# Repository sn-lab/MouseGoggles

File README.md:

**MouseGoggles**: A dual-SPI-display mouse-sized VR headset for mouse neuroscience and behavior research, powered by Raspberry Pi and the Godot game engine. Check out the paper at Nature Methods! https://www.nature.com/articles/s41592-024-02540-y

- Find a bug, have a suggestion, or want to make a feature request? Submit an [issue](https://github.com/sn-lab/MouseGoggles/issues) or start a [discussion](https://github.com/sn-lab/MouseGoggles/discussions)!

**Work in progess**

* Updating and improving [MouseGoggles EyeTrack 2.0](https://github.com/sn-lab/MouseGoggles/tree/main/Versions/EyeTrack/2.0) eye imaging quality and software improvements.

**Previous Updates**

* (Jan 2026) Added intial files for [MouseGoggles EyeTrack 2.0](https://github.com/sn-lab/MouseGoggles/tree/main/Versions/EyeTrack/2.0)! The design is now built around a single Raspberry Pi 5, aiming toward improving eye-tracking quality and a simpler assembly process (though eye-imaging quality is still being worked on).
  
* (May 2025) Big software updates to EyeTrack 1.1, including the first Godot project (2.1) which enables controlling and viewing the eye-tracking cameras from within the game engine! TCP/UDP communication between the Pis enable TTL outputs and eye-tracking videos to be controlled directly from VR experiment scripts.

* (Mar 2024) Added the [MouseGoggles EyeTrack](https://github.com/sn-lab/MouseGoggles/tree/main/Versions/EyeTrack/1.0) headset, for binocular eye/pupil tracking cameras integrated into the headset

# Building a MouseGoggles System

All versions of MouseGoggles were designed using as many readily available, off-the-shelf parts as possible, with only a minimal number of custom parts required to make assembly as simple as possible. To build a MouseGoggles system, navigate to the folder of the version you'd like to build in the [Versions](https://github.com/sn-lab/MouseGoggles/tree/main/Versions) folder and follow the included README for a comprehensive parts list, assembly guide, and software installation instructions. Since some parts included in earlier versions of the system have since been discontinued by the manufacturers, [Eyetrack version 2.0](https://github.com/sn-lab/MouseGoggles/tree/main/Versions/EyeTrack/2.0) is what we recommend building for all use-cases. Version 2.0 is built on an entirely new display platform (Raspberry Pi 5; mipi-dbi-spi) that future versions will be developed from. 

# About MouseGoggles

### The Raspberry Pi and Godot game engine

The heart of the MouseGoggles system is a [Raspberry Pi 4](https://www.raspberrypi.com/products/raspberry-pi-4-model-b/) running the [Godot](https://godotengine.org/) video game engine. Since the displays are relatively low resolution (240x240), an inexpensive single-board computer like a Raspberry Pi 4 is all that's needed to effectively render visual scenes at high (>=60 fps) framerates. The multiplatform game engine Godot makes it easy to create virtual scenes and develop experimental protocols. Examples included in this repo are experiments for visual cliff avoidance, reactions to looming stimuli of various size/velocity ratios, and the syndirectional rotational optomotor response to gratings of various spatial wavelengths. The views rendered for each display are controlled by separate in-game cameras which can be tied together to match the inter-eye distance and angle of a typical mouse. Custom display shaders warp the view from each camera to match the spherical distortion of the Fresnel lenses, intended to create a realistic and immersive experience for the mouse.

### The display driver

Based on a ["blazing fast" display driver](https://github.com/juj/fbcp-ili9341) for SPI-based displays, the driver included in this repository works by copying the HDMI framebuffer and streaming the image data to the connected displays connected on the Raspberry Pi's SPI port. This means that the headset displays are not limited to displaying what is rendered by Godot; in fact, whatever is displayed on the central 240x420 (WxH) pixel region of the screen is going to be streamed to the displays. If you want to create images or video with some other program, you just have to position it in the center of the display for it to be sent to the displays -- the top 240x210 sent to display 0 (on SPI0 chip-select 0) and the bottom 240x210 to display 1 (on SPI0 chip-select 1).

### The MouseGoggles 1.0 headset

To create an immersive, wide field-of-view (FOV) VR headset from the dual-display Raspberry Pi, a 3D-printed headset case angles the displays inwards and sets them behind Fresnel lenses. These lenses serve two functions: to allow the displays to be positioned very close (<15 mm) to the mouse's eyes while still maintaining a comfortable infinity focal distance, and to spherically distort the displays to cover a wide FOV around each eye. Viewing angles from 0-70 degrees (0-52.5 degrees on the chipped side of the circular display) are linearly mapped onto the 240x210 circular display, resulting in an angular resolution of ~0.64 deg/pixel. With the 2 displays angled 45 degrees inward from straight ahead, the binocular headset covers a wide FOV: 140 degrees vertical and 230 degrees horizontal, with ~25 degrees of binocular overlap. Even greater horizontal FOVs are possible with greater display angles. This headset is the first official version of MouseGoggles (1.0), but newer versions have been developed which add new functionality, such as a smaller form-factor headset detached from the Raspberry Pi (1.1-1.2, 1.5), adjustable inter-eye distance (1.2-1.5), and an easier to assemble design (1.5). For more details on each MouseGoggles version, see the [Versions](https://github.com/sn-lab/MouseGoggles/tree/main/Versions) folder.

### MouseGoggles Mono 1.0

In addition to the binocular MouseGoggles system, a monocular eyepiece version can be built using a single display, lens, and microcontroller. Where the headset is ideal for complex virtual reality experiments and behavioral research, the monocular display is ideal for simple visual stimulation for basic visual neuroscience applications. The fast microcontroller [Teensy4.0](https://www.pjrc.com/store/teensy40.html) and [Adafruit graphics library](https://learn.adafruit.com/adafruit-gfx-graphics-library/overview) is used to display simple shapes and moving patterns such as drifting gratings and flickers. For more details, see [Versions/Mono/1.0]().

### Treadmills

The MouseGoggles VR headset was developed and tested using a two different treadmills for simulated walking: the spherical treadmill setup as described [here](https://pubmed.ncbi.nlm.nih.gov/19829374/) and the linear treadmill described [here](https://github.com/janelia-experimental-technology/Rodent-Belt-Treadmill/tree/main). These treadmills use sensors to detect treadmill motion and a microcontroller to transmit this movement information to external devices. By modifying the microcontroller code, we can adapt these systems to send treadmill motion to the Raspberry Pi over USB through computer mouse emulation. Forward movement (i.e. "pitch" of the spherical treadmill, or any movement of the linear treadmill) is mapped as mouse y movement, turning (i.e. "yaw" of the spherical treadmill) is mapped as x movement, and sideways motion (i.e. "roll" of the spherical treadmill) is mapped as mouse scroll wheel movement. The Godot game engine converts these detected mouse movement events into the corresponding camera movements in the virtual scene. This setup allows the human user to test the game environments and experiments using a standard computer mouse or touchpad, and to use this VR system with any type of treadmill control system that can be translated through the standard USB mouse communication protocol. To set up one of these treadmill systems with MouseGoggles (including adding a headbar and mount to head-fix a mouse above the treadmill), see the [README](https://github.com/sn-lab/MouseGoggles/blob/main/Other%20Hardware/Installation%20README.md) in the [Other Hardware](https://github.com/sn-lab/MouseGoggles/tree/main/Other%20Hardware) folder.

# Published Data

Multiple datasets have been collected for validating and testing different aspects of the MouseGoggles system for neuroscience applications, including 2-photon imaging for visual stimulation, hippocampal electrophysiology for place cell activity during virtual navigation, and video recordings of mouse behaviors during looming stimulus presentation. Check out our [preprint on Research Square](https://doi.org/10.21203/rs.3.rs-3301474/v1) for explanation and visualization of these datasets. Data, metadata, and code to process and analyze these datasets are included in the [Published Data](https://github.com/sn-lab/MouseGoggles/tree/main/Published%20Data) folder of this repository; large raw data files unsuitable for github are hosted on [Figshare](https://figshare.com/articles/dataset/Raw_image_files/24039021). 
To reproduce the published results from each of these datasets, follow the instructions in the [Description of Contents](https://github.com/sn-lab/MouseGoggles/blob/main/Published%20Data/Description%20of%20Contents.md) file, noting the software dependencies listed here:

```
* Matlab 2022b
* Python 2.8.8
* suite2p (suite2p.org)
* https://github.com/misaacson01/NoRMCorre
* https://github.com/lolaBerkowitz/SNLab_ephys
* https://github.com/nelpy/nelpy
* https://github.com/ryanharvey1/neuro_py
* https://github.com/ryanharvey1/ripple_heterogeneity
```

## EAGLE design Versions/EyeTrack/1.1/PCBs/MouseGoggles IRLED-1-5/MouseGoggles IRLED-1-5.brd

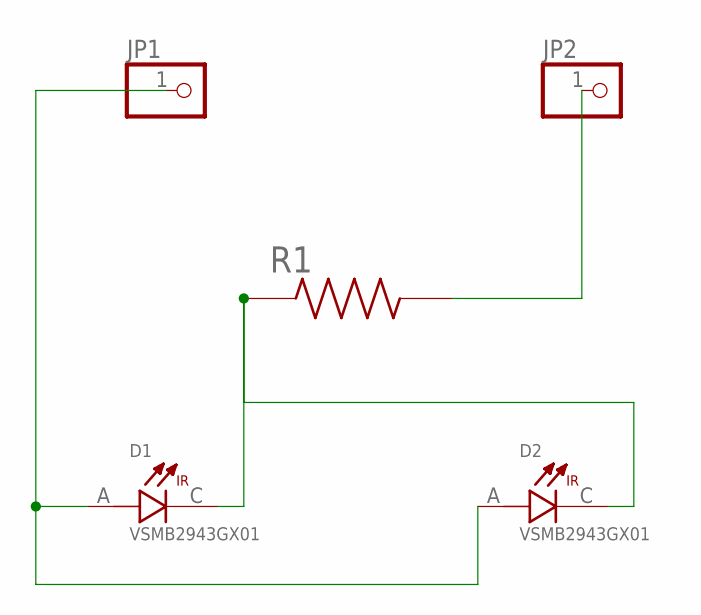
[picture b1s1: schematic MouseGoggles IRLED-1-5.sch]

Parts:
D1, D2: VSMB2943GX01; DIO_VSMB2943GX01
JP1, JP2: PINHD-1X1; 1X01
R1: RC0805FR-07100RL; RESC2012X60N

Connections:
unnamed: JP2.1, R1.2
unnamed: D1.A, D2.A, JP1.1
unnamed: D1.C, D2.C, R1.1

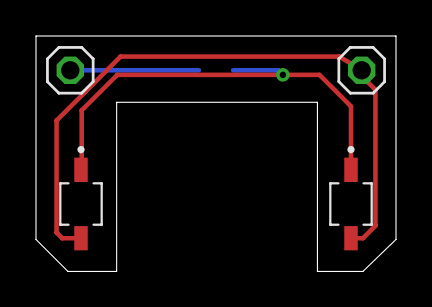
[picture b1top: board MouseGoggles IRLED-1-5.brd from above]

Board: 2 copper layers, 20.0 x 13.1 mm, 5 parts (1 on the bottom side), 3 nets.

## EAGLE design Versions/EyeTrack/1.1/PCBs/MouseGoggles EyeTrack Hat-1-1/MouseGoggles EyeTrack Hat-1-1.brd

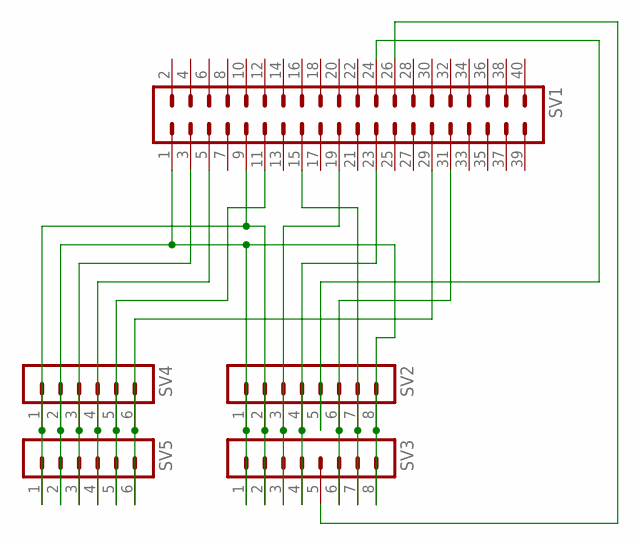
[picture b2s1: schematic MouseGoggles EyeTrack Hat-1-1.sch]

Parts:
SV1: MA20-2
SV2, SV3: MA08-1
SV4, SV5: MA06-1

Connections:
unnamed: SV1.1, SV2.1, SV2.8, SV3.1, SV3.8, SV4.2, SV5.2
unnamed: SV1.9, SV2.2, SV3.2, SV4.1, SV5.1
unnamed: SV1.19, SV2.3, SV3.3
unnamed: SV1.23, SV2.4, SV3.4
unnamed: SV1.24, SV2.5
unnamed: SV1.26, SV3.5
unnamed: SV1.31, SV2.6, SV3.6
unnamed: SV1.15, SV2.7, SV3.7
unnamed: SV1.3, SV4.3, SV5.3
unnamed: SV1.5, SV4.4, SV5.4
unnamed: SV1.11, SV4.5, SV5.5
unnamed: SV1.29, SV4.6, SV5.6

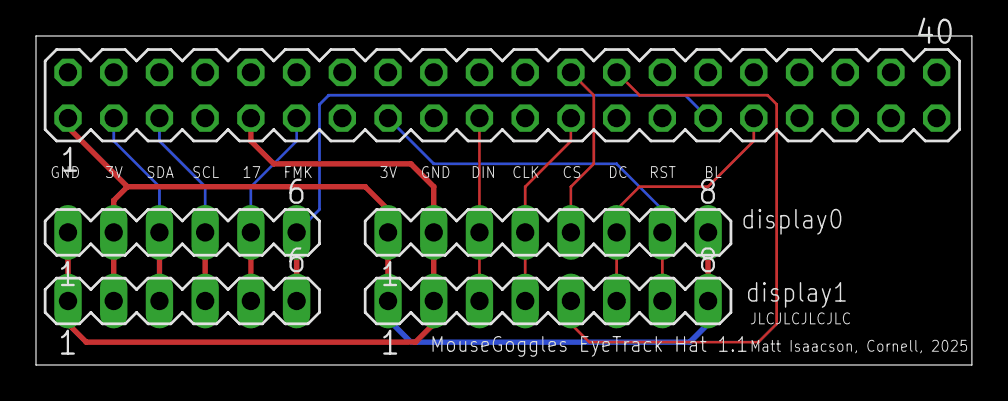
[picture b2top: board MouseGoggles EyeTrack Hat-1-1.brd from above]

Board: 2 copper layers, 52.0 x 18.3 mm, 5 parts (0 on the bottom side), 12 nets.

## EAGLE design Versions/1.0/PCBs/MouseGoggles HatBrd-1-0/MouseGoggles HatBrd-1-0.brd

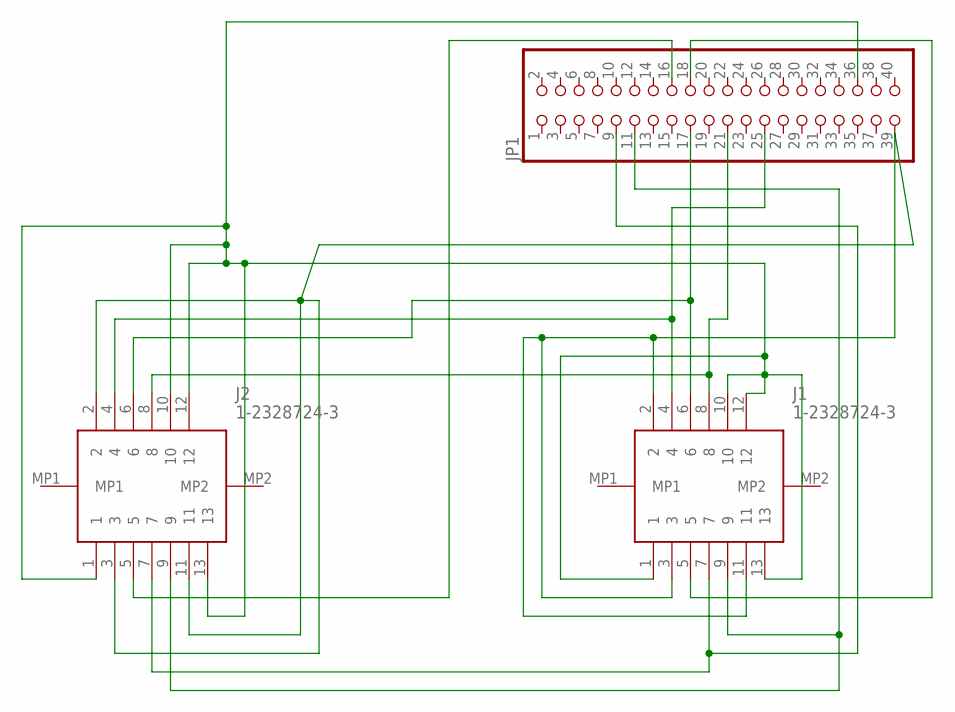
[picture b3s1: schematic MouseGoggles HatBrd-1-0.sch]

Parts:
J1, J2: 1-2328724-3; 123287243
JP1: PINHD-2X20-BIG; 2X20-BIG

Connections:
unnamed: J1.2, J1.3, J1.11, J2.2, J2.3, J2.11, JP1.39
unnamed: J1.8, J2.8, JP1.21
unnamed: J1.6, J2.6, JP1.17
unnamed: J1.5, JP1.18
unnamed: J1.1, J1.10, J1.12, J1.13, J2.1, J2.10, J2.12, J2.13, JP1.36
unnamed: J1.4, J2.4, JP1.25
unnamed: J1.7, J2.7, JP1.9
unnamed: J1.9, J2.9, JP1.11
unnamed: J2.5, JP1.16

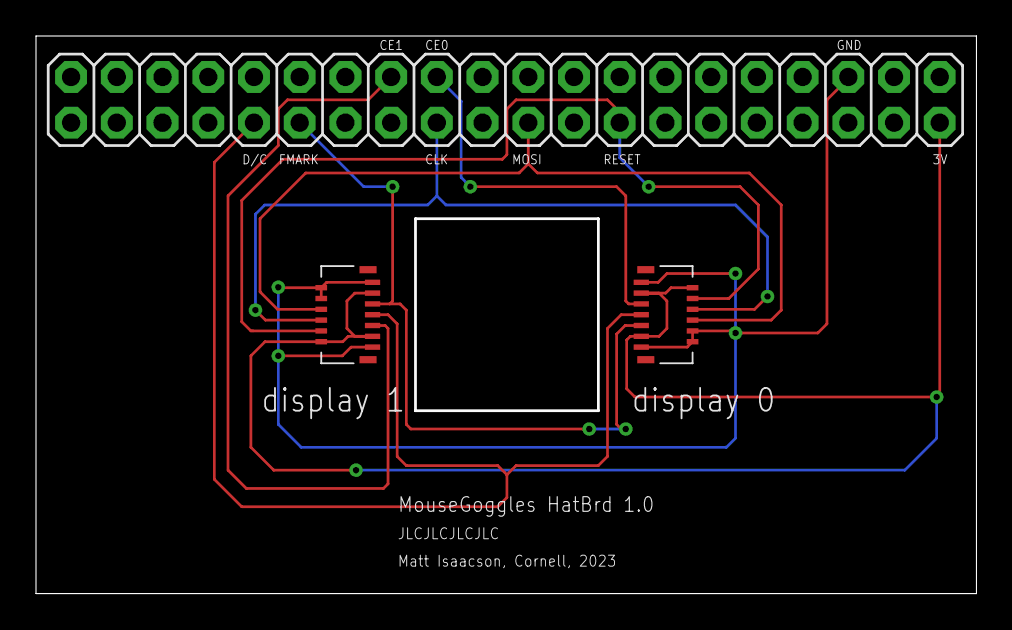
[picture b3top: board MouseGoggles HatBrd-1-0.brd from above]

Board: 2 copper layers, 52.1 x 30.8 mm, 3 parts (0 on the bottom side), 9 nets.

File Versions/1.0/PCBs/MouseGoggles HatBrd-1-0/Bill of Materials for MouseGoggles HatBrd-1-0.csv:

Comment,Designator,Package,JLCPCB Part #
FPC-CONN,J1,-,C3170061
FPC-CONN,J2,-,C3170061

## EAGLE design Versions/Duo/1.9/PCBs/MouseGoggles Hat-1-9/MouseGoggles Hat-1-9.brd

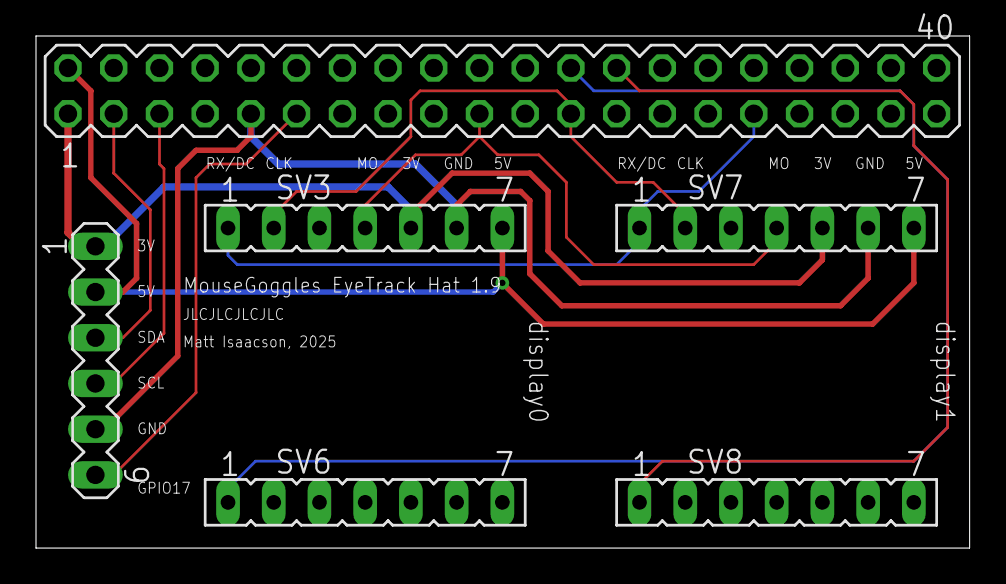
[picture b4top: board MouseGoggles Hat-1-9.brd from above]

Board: 2 copper layers, 51.9 x 28.4 mm, 6 parts (0 on the bottom side), 11 nets.

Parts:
SV1: MA20-2
SV3, SV6, SV7, SV8: FE07
SV4: MA06-1

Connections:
unnamed: SV1.1, SV3.5, SV4.1, SV7.5
unnamed: SV1.9, SV3.6, SV4.5, SV7.6
unnamed: SV1.23, SV3.2, SV7.2
unnamed: SV1.24, SV6.1
unnamed: SV1.26, SV8.1
unnamed: SV1.31, SV3.1, SV7.1
unnamed: SV1.19, SV3.4, SV7.4
unnamed: SV1.3, SV4.3
unnamed: SV1.5, SV4.4
unnamed: SV1.11, SV4.6
unnamed: SV1.2, SV3.7, SV4.2, SV7.7

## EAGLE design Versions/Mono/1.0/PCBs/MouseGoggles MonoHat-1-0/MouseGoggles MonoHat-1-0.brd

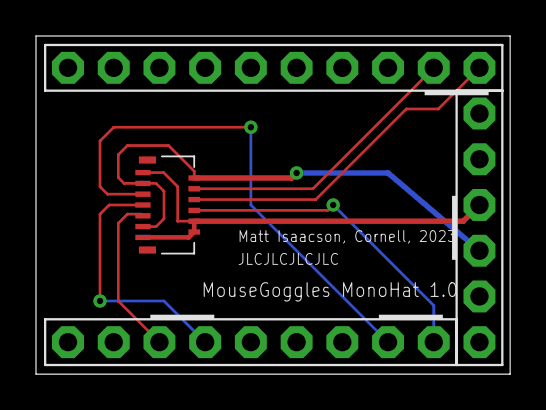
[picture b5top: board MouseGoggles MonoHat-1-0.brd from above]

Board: 2 copper layers, 26.3 x 18.8 mm, 4 parts (0 on the bottom side), 8 nets.

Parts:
J1: 1-2328724-3; 123287243
JP1: 1X09-BIG
JP6: 1X06-BIG
U$1: PINHD-1X10; 1X10-BIG

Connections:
unnamed: J1.1, J1.10, J1.12, J1.13, JP6.3
unnamed: J1.2, J1.3, J1.11, JP6.4
unnamed: J1.5, JP1.2
unnamed: J1.6, U$1.1
unnamed: J1.8, JP1.1
unnamed: J1.4, U$1.2
unnamed: J1.7, JP1.6
unnamed: J1.9, JP1.7

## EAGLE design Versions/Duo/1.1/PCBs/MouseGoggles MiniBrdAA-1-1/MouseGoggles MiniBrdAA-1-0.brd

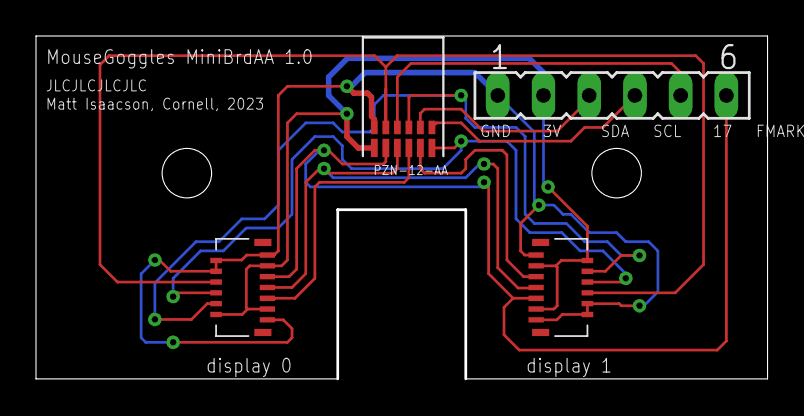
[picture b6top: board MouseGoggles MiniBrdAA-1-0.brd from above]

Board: 2 copper layers, 40.5 x 19.0 mm, 4 parts (0 on the bottom side), 12 nets.

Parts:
J1, J2: 1-2328724-3; 123287243
SV1: FE06
U$1: PZN_12_AA; OMN_PZN_NANO_6X2

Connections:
unnamed: J1.2, J1.3, J1.11, J2.2, J2.3, J2.11, SV1.2, U$1.P$2
unnamed: J1.1, J1.10, J1.12, J1.13, J2.1, J2.10, J2.12, J2.13, SV1.1, U$1.P$1
unnamed: J1.9, J2.9, SV1.6, U$1.P$4
unnamed: J1.7, J2.7, U$1.P$6
unnamed: J1.5, U$1.P$8
unnamed: J2.5, U$1.P$10
unnamed: J1.6, J2.6, U$1.P$12
unnamed: J1.8, J2.8, U$1.P$3
unnamed: J1.4, J2.4, U$1.P$7
unnamed: SV1.5, U$1.P$5
unnamed: SV1.3, U$1.P$9
unnamed: SV1.4, U$1.P$11

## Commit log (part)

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2022-11-02 Added Godot Project
2022-11-02 Added working files from test Raspberry Pi
2022-11-02 Added 2xSPI fbcp display driver
2022-11-09 Added hardware files
2022-11-09 rearrange hardware files; update readme
2022-11-09 Added monocular display code; demo gif
2022-11-09 Added treadmill controller code
2022-11-10 Add images
2022-11-10 Add 3D prints
2022-11-11 Added images
2022-11-12 Added zipped PCB files
2022-12-15 Updated 3D print files, monocular display software instructions
2022-12-19 Godot project update
2023-01-13 Added Godot project V0.7
2023-01-14 Update loom movement threshold based on test data
2023-06-08 Update README.md
    typos
2023-06-13 Added headset assembly text instructions
2023-06-13 Fixed innacuracy in gdshader; Added Pi header to parts list
2023-06-15 Added info on pinouts
2023-06-26 Added test assembly files
2023-07-10 Added test driver files for st7789v2
2023-07-12 bugfix attempt for offset and flipped displays
2023-07-25 Added files
2023-08-11 Godot project V1.0: more experiments, better logging, bug fixes
2023-09-01 Add published data/metadata
2023-09-02 Added files for small form factor headset
2023-09-19 Added references to preprint
2023-10-28 Added assembly photos
2023-10-30 Update README.md
    Not yet validated for newest Raspberry Pi OS (bookworm), tested OS version (bullseye) is now legacy.
2023-11-10 Updated files for small form factor headset
2023-11-10 Updated small form factor headset 3D prints
2023-11-25 Added support for st7789v2
2023-11-29 Added support for 240x240 Waveshare GC9A01 display
2023-11-29 Lowered default SPI rate and frame rate
2023-12-05 Added testing shaders for waveshare displays
2023-12-11 Deleted fbcp-st7789 driver folder (obsolete)
2023-12-11 Added ability to scale down red pixel color in waveshare display shaders
2024-01-14 Added files for MouseGoggles version 1.5
2024-01-31 Updated versions
    -Added new MouseGoggles versions: 1.0-1.5
    -Added design files (3D .step, PCB schematic, layout, eagle projects) for all versions
    -Restructured assembly/installation instructions to be version-specific
    -Added "Other Hardware", including linear treadmill and headbars/mounts
    -Removed outdated Godot projects
    -
2024-01-31 Fixed links
2024-03-26 Added EyeTracking! Reformatted versions for Mono/Duo/EyeTrack models
2024-03-26 Updated readmes for eye tracking
2024-03-28 Update to Godot project 1.6; add Intro to Godot
2024-03-28 Added code and instructions for headset rotation feedback
2024-08-01 Added comments for ADNS3080 debugging code
2024-09-12 Uploaded Godot Project 1.8 (rotating gratings, linear track with loom)
2025-02-05 Added files for EyeTrack 1,1
2025-02-13 Update IRLED board
2025-02-21 Add assembly images
2025-02-27 added Godot Project 2.0
2025-03-03 Update introduction
2025-05-06 Update EyeTrack 1.1 and Godot Project 2.1 for TCP/UDP eye-tracking communication
2025-05-21 software update for improved eye-tracking
    - Better TCP/UDP communication
    - Custom binary eye-tracking video creation and transfer
    -improved scene select layout
    -New receptive field mapping experimennt
2025-06-10 Godot bug fixes
2025-06-11 Bug fixes; window now correctly positioned on "run" instead of "edit"
2025-06-11 Updated instructions for bypassing the Godot editor
2025-06-12 No longer transferring videos to the Pi 4 to avoid disk space issues
2025-06-12 Update instructions on handling recorded video
2025-06-12 Fixed offset (viewport not precisely centered on display)
2025-07-04 Bug fixes
2025-07-04 Updated instructions for the latest Godot downloads
2025-07-04 Updated instructions
2025-07-04 Updated instructions on camera availability
2025-10-01 Added initial files for Duo V1.9 and EyeTrack V1.9
2026-01-23 Added initial design files for EyeTrack 2.0
2026-01-28 Update config file instructions
2026-01-28 Added config for dual cameras
2026-01-28 Added details for correct SPI screen orientation
2026-01-28 Update images for EyeTrack 2.0 in README
2026-01-28 Update display installation instructions
    Updated instructions for downloading and setting up the Godot game engine, including changes to the display driver setup.
2026-01-28 Upload Godot editor and Godot Project 2.2 for EyeTrack 2.0
2026-01-28 Updated software setup instructions
2026-02-02 Updated LensClip, Bracket, and Assembly instructions
2026-02-02 Fix file paths in README for installation instructions
    Updated file paths in installation instructions for Raspberry Pi.
2026-02-02 Fix Display 2 pin assignments and update instructions
    Corrected pin assignments for Display 2 and improved clarity in installation instructions.
2026-02-03 Revise assembly and wiring instructions in README
    Updated images and instructions for assembling and wiring MouseGoggles EyeTrack 2.0.
2026-02-03 Added assembly images
2026-02-03 Add issue reporting link
2026-02-09 Update video recording file path and remove TCP server
    Refactor video file handling to save in a specified log directory and remove TCP server functionality.
2026-02-09 Revise camera installation instructions
    Updated wiring instructions for displays and cameras, and clarified steps to start the camera controller and Godot game engine.
2026-02-09 Set common defaults
    default: 50-deg bracket; horizontal headset position (not pitched up or down); eye-tracking recording enabled
2026-02-10 Revise EyeTrack 2.0 assembly notes for clarity
    Updated the description of the EyeTrack 2.0 assembly process to clarify the current state of eye imaging quality and the need for external IR illumination.
2026-02-22 Added new IR pupil imaging design
    - Added new 3D designs to support IR LEDs
    - Updated Godot project to remove red eye illumination
    - Updated instructions to reflect these changes
2026-03-27 Added new experiment: videoPlayer
    videoPlayer experiment allows playing a flat 2D video in the VR scene. Parameters allow adjusting the size and position of the virtual video screen (to match the FOV of the video), how to handle play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
2026-06-08 Improved camera setting controls
2026-06-08 Added simulated visualization of Mono stimuli
2026-06-08 Added new IR-sensitive camera; improved camera scripts; instructions for calibrating cameras
